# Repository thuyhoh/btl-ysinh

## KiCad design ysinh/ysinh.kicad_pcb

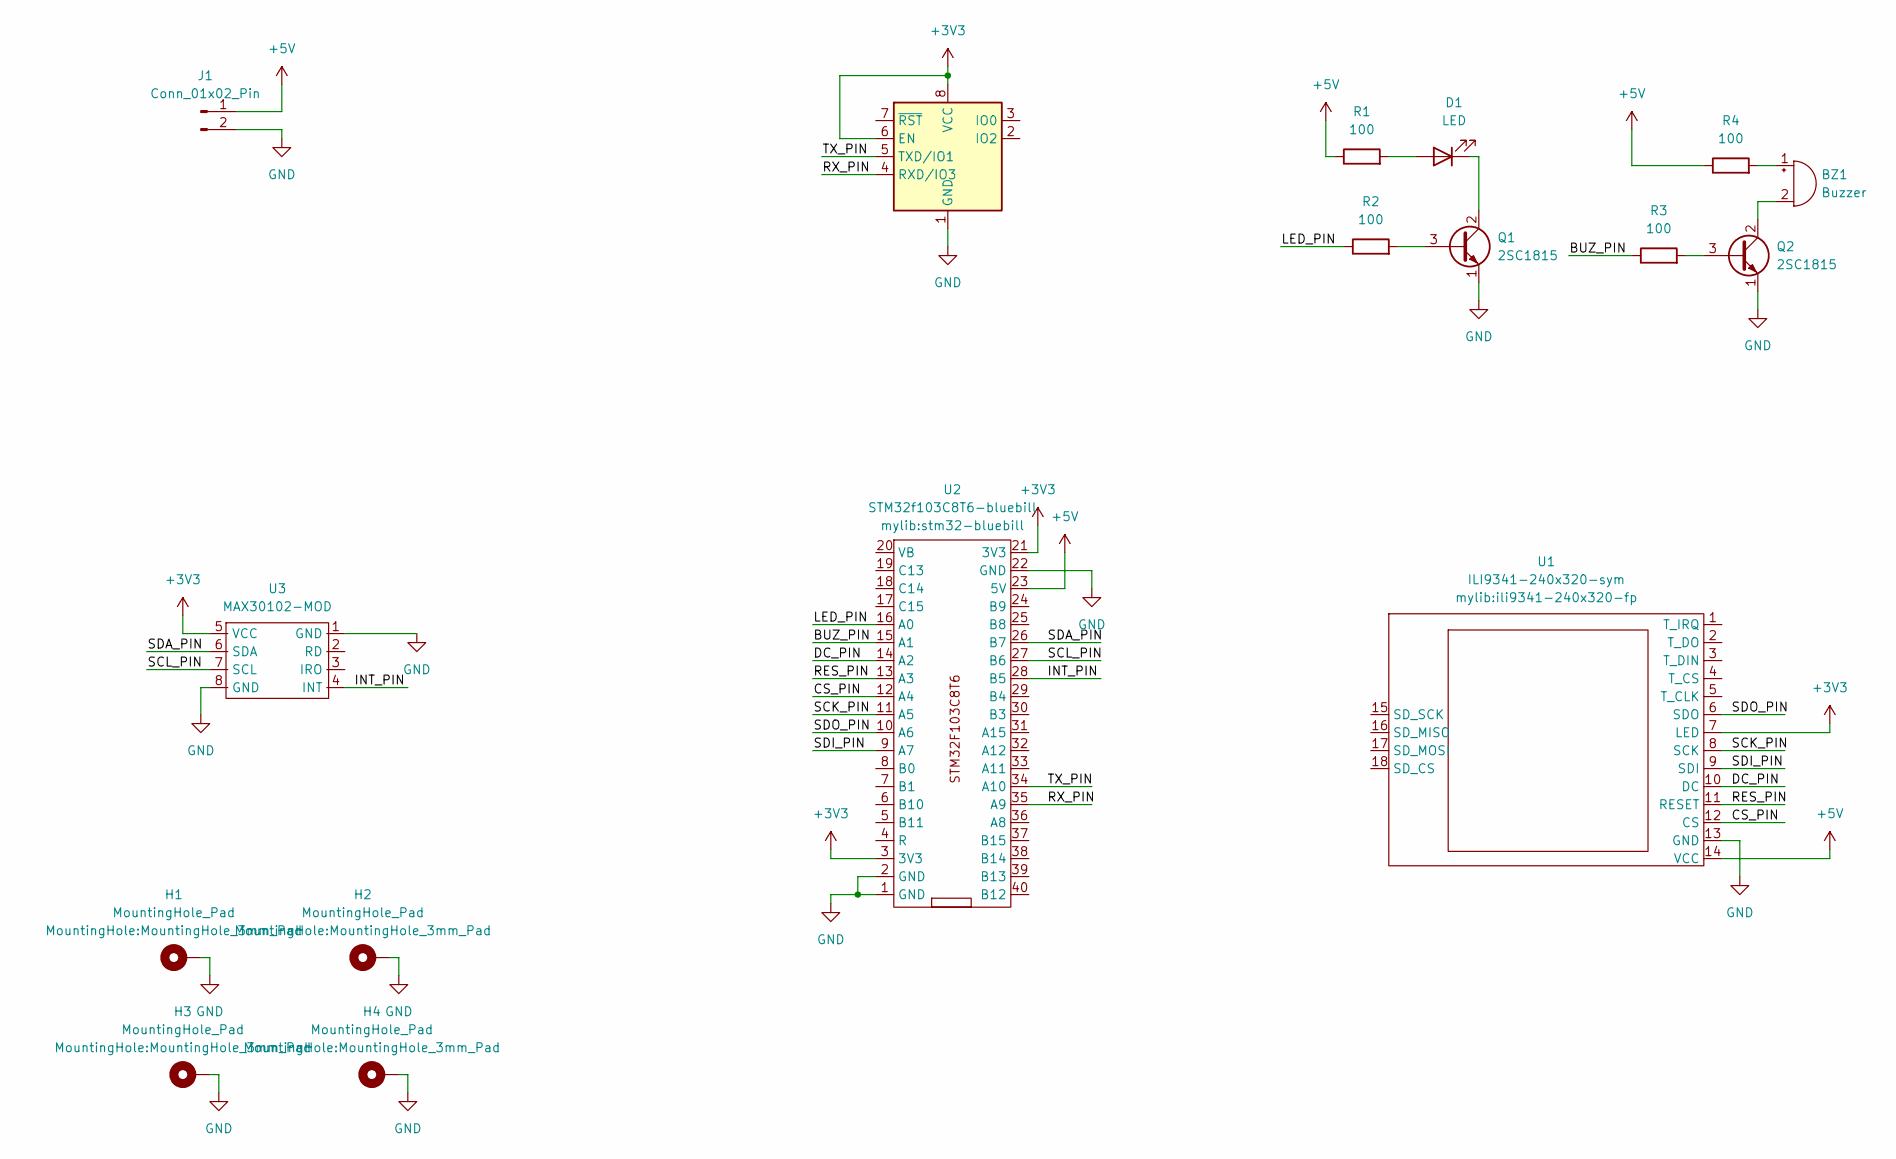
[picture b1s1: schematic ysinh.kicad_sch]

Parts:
BZ1: Buzzer; Buzzer_12x9.5RM7.6
D1: LED; LED_D3.0mm_Horizontal_O1.27mm_Z10.0mm
H1, H2, H3, H4: MountingHole_Pad; MountingHole_3mm_Pad
J1: Conn_01x02_Pin; PinHeader_1x02_P2.54mm_Vertical
Q1, Q2: 2SC1815; TO-92_Inline
R1, R2, R3, R4: 100; R_Axial_DIN0207_L6.3mm_D2.5mm_P10.16mm_Horizontal
U1: ILI9341-240x320-sym; ili9341-240x320-fp
U2: STM32f103C8T6-bluebill; stm32-bluebill
U3: MAX30102-MOD; max30102-mod-fp
U4: ESP-01; esp01-mod-fp

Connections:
+3V3: U1.7 (LED), U2.3 (3V3), U2.21 (3V3), U3.5 (VCC), U4.6 (EN), U4.8 (VCC)
+5V: J1.1, R1.1, R4.1, U1.14 (VCC), U2.23 (5V)
/BUZ_PIN: R3.1, U2.15 (A1)
/CS_PIN: U1.12 (CS), U2.12 (A4)
/DC_PIN: U1.10 (DC), U2.14 (A2)
/INT_PIN: U2.28 (B5), U3.4 (INT)
/LED_PIN: R2.1, U2.16 (A0)
/RES_PIN: U1.11 (RESET), U2.13 (A3)
/RX_PIN: U2.35 (A9), U4.4 (RXD/IO3)
/SCK_PIN: U1.8 (SCK), U2.11 (A5)
/SCL_PIN: U2.27 (B6), U3.7 (SCL)
/SDA_PIN: U2.26 (B7), U3.6 (SDA)
/SDI_PIN: U1.9 (SDI), U2.9 (A7)
/SDO_PIN: U1.6 (SDO), U2.10 (A6)
/TX_PIN: U2.34 (A10), U4.5 (TXD/IO1)
GND: H1.1 (1_1), H2.1 (1_1), H3.1 (1_1), H4.1 (1_1), J1.2, Q1.1 (E), Q2.1 (E), U1.13 (GND), U2.1 (GND), U2.2 (GND), U2.22 (GND), U3.1 (GND), U3.8 (GND), U4.1 (GND)
unnamed: BZ1.1 (+), R4.2
unnamed: BZ1.2 (-), Q2.2 (C)
unnamed: D1.2 (A), R1.2
unnamed: D1.1 (K), Q1.2 (C)
unnamed: Q1.3 (B), R2.2
unnamed: Q2.3 (B), R3.2

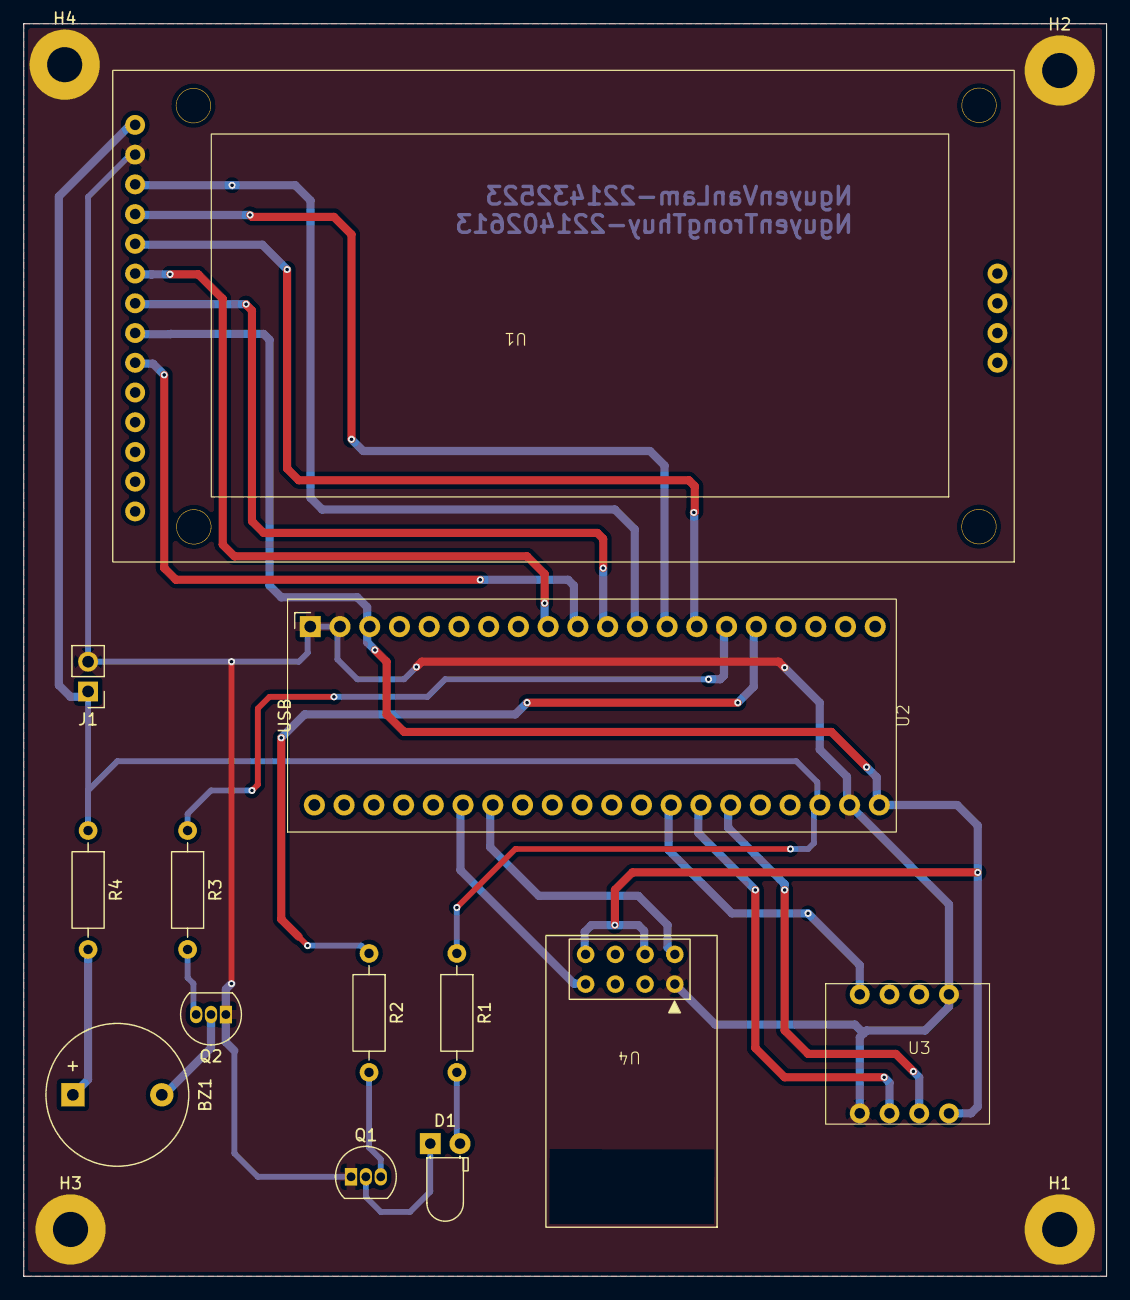
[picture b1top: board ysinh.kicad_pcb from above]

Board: 2 copper layers, 92.5 x 107.0 mm, 17 parts (0 on the bottom side), 22 nets.
